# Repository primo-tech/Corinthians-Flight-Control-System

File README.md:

# Corinthians-Flight-Control-System
Raspberry Pi Zero W + STM32F103C8T6 Based Flight Control System For Fixed wing and Multi-Rotor UAVs

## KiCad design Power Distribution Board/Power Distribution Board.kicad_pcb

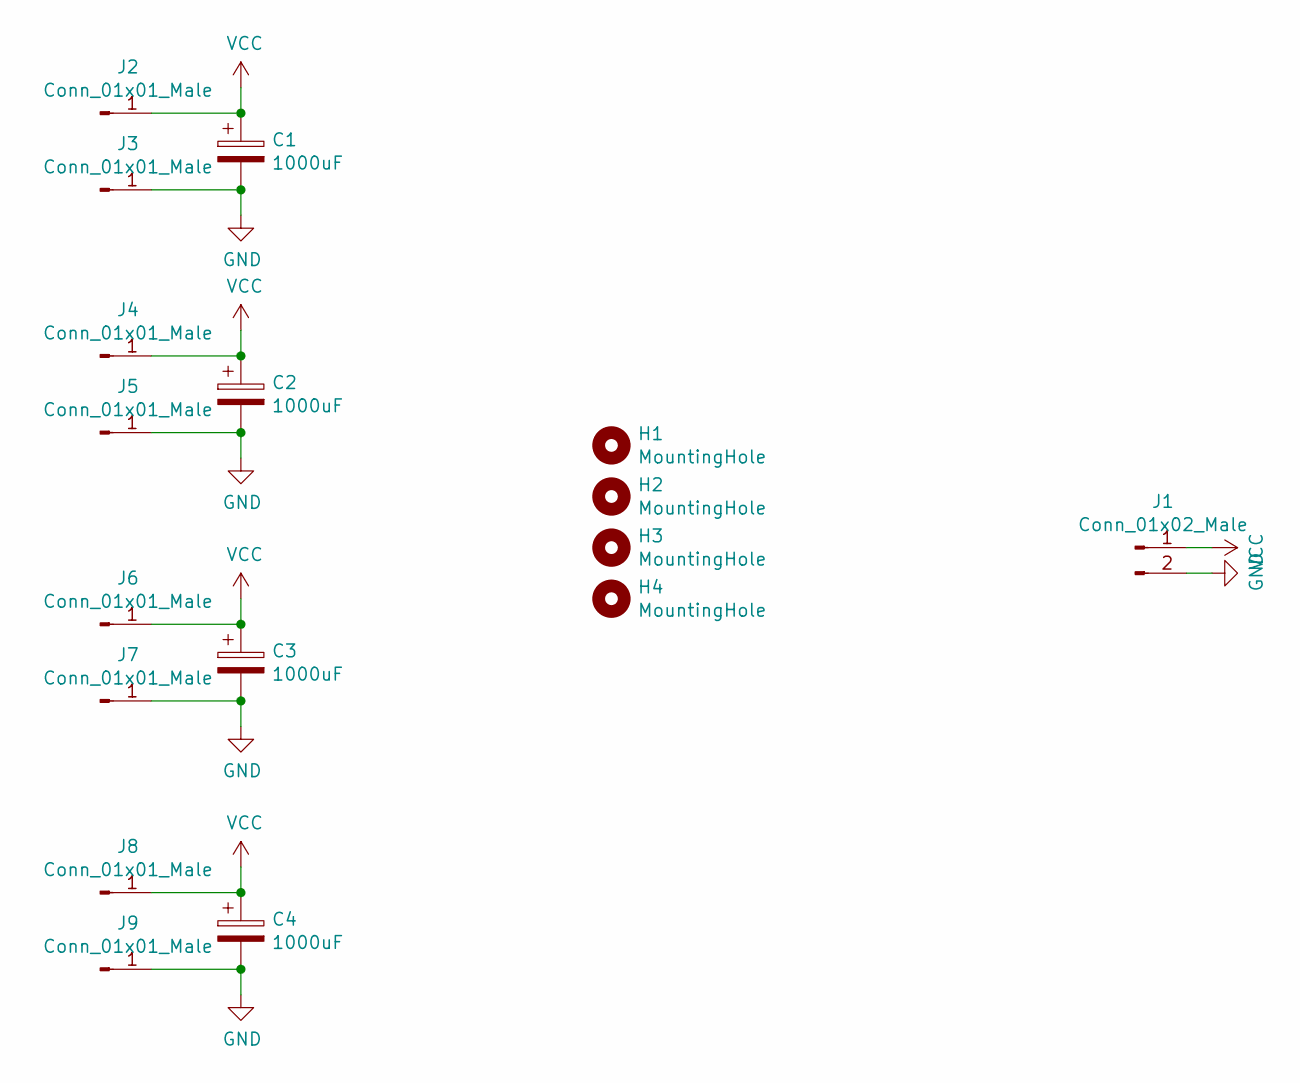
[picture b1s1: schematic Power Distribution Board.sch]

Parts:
C1, C2, C3, C4: 1000uF; CP_Radial_D10.0mm_P7.50mm
H1, H2, H3, H4: MountingHole; MountingHole_3.2mm_M3
J1: Conn_01x02_Male; AMASS_XT60-M_1x02_P7.20mm_Vertical
J2, J3, J4, J5, J6, J7, J8, J9: Conn_01x01_Male; TestPoint_Pad_4.0x4.0mm

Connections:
GND: C1.2, C2.2, C3.2, C4.2, J1.2, J3.1, J5.1, J7.1, J9.1
VCC: C1.1, C2.1, C3.1, C4.1, J1.1, J2.1, J4.1, J6.1, J8.1

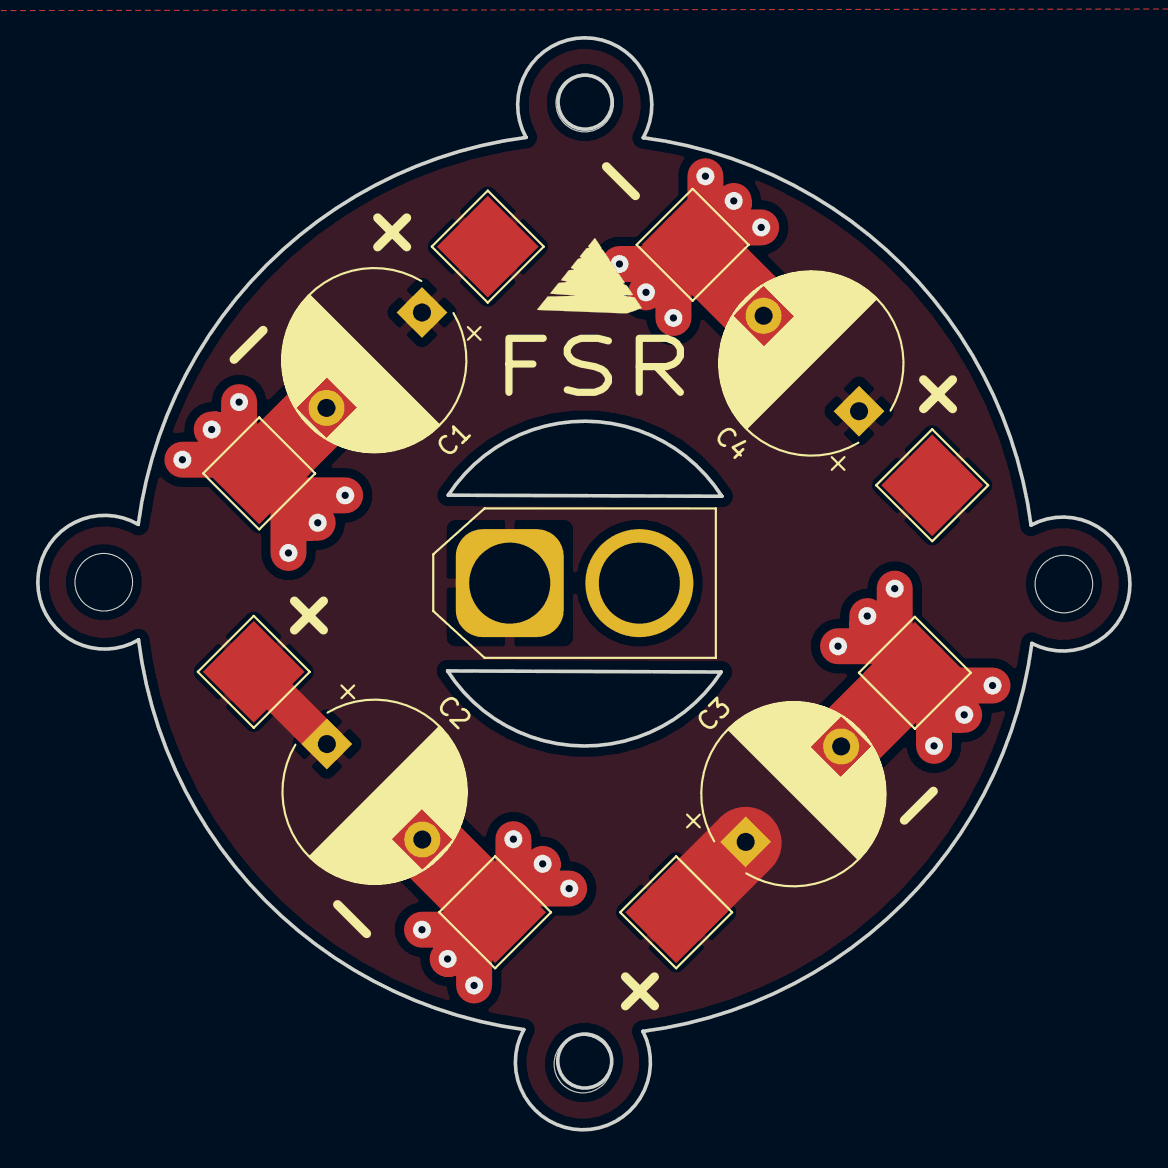
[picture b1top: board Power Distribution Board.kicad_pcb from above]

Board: 2 copper layers, 60.7 x 60.7 mm, 17 parts (0 on the bottom side), 2 nets.

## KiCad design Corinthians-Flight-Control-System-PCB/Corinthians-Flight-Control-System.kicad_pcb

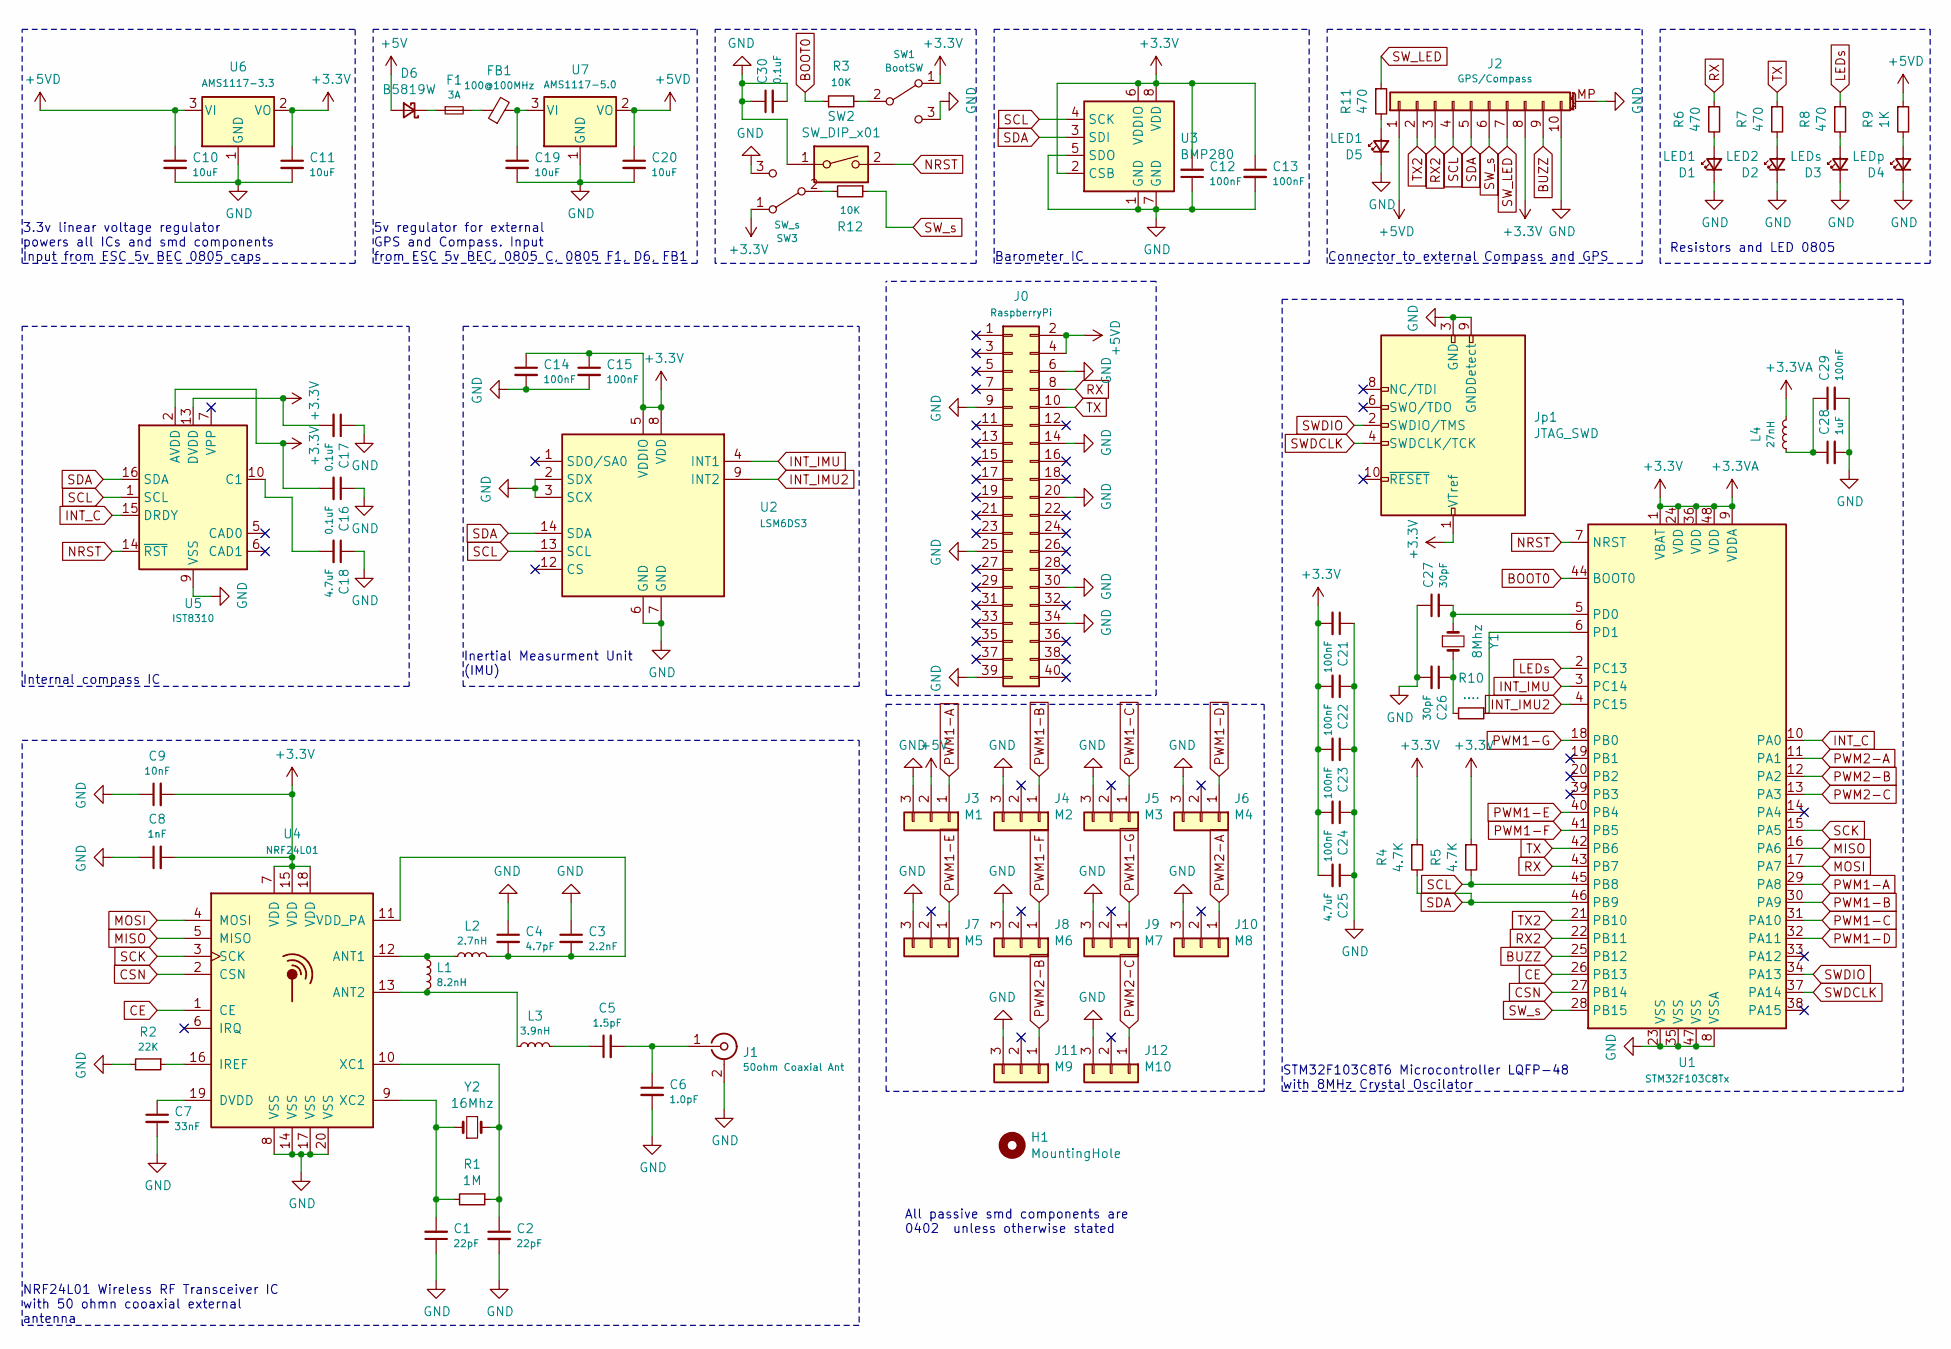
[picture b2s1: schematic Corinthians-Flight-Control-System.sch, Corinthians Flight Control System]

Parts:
C1, C2: 22pF; C_0402_1005Metric
C3: 2.2nF; C_0402_1005Metric
C4: 4.7pF; C_0402_1005Metric
C5: 1.5pF; C_0402_1005Metric
C6: 1.0pF; C_0402_1005Metric
C7: 33nF; C_0402_1005Metric
C8: 1nF; C_0402_1005Metric
C9: 10nF; C_0402_1005Metric
C10, C11, C19, C20: 10uF; C_0805_2012Metric
C12, C13, C14, C15, C21, C22, C23, C24, C29: 100nF; C_0402_1005Metric
C16, C17, C30: 0.1uF; C_0402_1005Metric
C18, C25: 4.7uF; C_0402_1005Metric
C26, C27: 30pF; C_0402_1005Metric
C28: 1uF; C_0402_1005Metric
D1: LED1; LED_0805_2012Metric
D2: LED2; LED_0805_2012Metric
D3: LEDs; LED_0805_2012Metric
D4: LEDp; LED_0805_2012Metric
D5: LED1; LED_0402_1005Metric
D6: B5819W; D_0805_2012Metric
F1: 3A; Fuse_0805_2012Metric
FB1: 100@100MHz; L_0805_2012Metric
H1: MountingHole; MountingHole_3.2mm_M3
J0: RaspberryPi; PinSocket_2x20_P2.54mm_Vertical
J1: 50ohm Coaxial Ant; SMA_Molex_73251-2200_Horizontal
J2: GPS/Compass; JST_GH_BM10B-GHS-TBT_1x10-1MP_P1.25mm_Vertical
J3: M1; PinHeader_1x03_P2.54mm_Vertical
J4: M2; PinHeader_1x03_P2.54mm_Vertical
J5: M3; PinHeader_1x03_P2.54mm_Vertical
J6: M4; PinHeader_1x03_P2.54mm_Vertical
J7: M5; PinHeader_1x03_P2.54mm_Vertical
J8: M6; PinHeader_1x03_P2.54mm_Vertical
J9: M7; PinHeader_1x03_P2.54mm_Vertical
J10: M8; PinHeader_1x03_P2.54mm_Vertical
J11: M9; PinHeader_1x03_P2.54mm_Vertical
J12: M10; PinHeader_1x03_P2.54mm_Vertical
Jp1: JTAG_SWD; PinHeader_2x05_P2.54mm_Vertical
L1: 8.2nH; L_0402_1005Metric
L2: 2.7nH; L_0402_1005Metric
L3: 3.9nH; L_0402_1005Metric
L4: 27nH; L_0402_1005Metric
R1: 1M; R_0402_1005Metric
R2: 22K; R_0402_1005Metric
R3, R12: 10K; R_0402_1005Metric
R4, R5: 4.7K; R_0402_1005Metric
R6, R7, R8: 470; R_0805_2012Metric
R9: 1K; R_0805_2012Metric
R10: ....; R_0402_1005Metric
R11: 470; R_0402_1005Metric
SW1: BootSW; SW_DIP_SPSTx01_Slide_Copal_CVS-01xB_W5.9mm_P1mm
SW2: SW_DIP_x01; SW_SPST_CK_RS282G05A3
SW3: SW_s; SW_DIP_SPSTx01_Slide_Copal_CVS-01xB_W5.9mm_P1mm
U1: STM32F103C8Tx; LQFP-48_7x7mm_P0.5mm
U2: LSM6DS3; LGA-14_3x2.5mm_P0.5mm_LayoutBorder3x4y
U3: BMP280; Bosch_LGA-8_2x2.5mm_P0.65mm_ClockwisePinNumbering
U4: NRF24L01; QFN-20-1EP_4x4mm_P0.5mm_EP2.5x2.5mm
U5: IST8310; LGA-16_3x3mm_P0.5mm
U6: AMS1117-3.3; SOT-223-3_TabPin2
U7: AMS1117-5.0; SOT-223-3_TabPin2
Y1: 8Mhz; Crystal_SMD_0603-2Pin_6.0x3.5mm
Y2: 16Mhz; Crystal_SMD_0603-2Pin_6.0x3.5mm

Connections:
+3.3VA: C8.2, C9.2, C11.1, C12.2, C13.1, C14.1, C15.1, C16.2, C17.2, C21.2, C22.2, C23.2, C24.2, C25.2, J2.8, Jp1.1 (VTref), L4.2, R4.1, R5.1, SW1.1 (A), SW3.1 (A), U1.1 (VBAT), U1.9 (VDDA), U1.24 (VDD), U1.36 (VDD), U1.48 (VDD), U2.5 (VDDIO), U2.8 (VDD), U3.2 (CSB), U3.6 (VDDIO), U3.8 (VDD), U4.7 (VDD), U4.15 (VDD), U4.18 (VDD), U5.2 (AVDD), U5.13 (DVDD), U6.2 (VO)
+5V: D6.2 (A), J3.2
+5VD: C10.1, C20.1, J0.2, J0.4, J2.1, R9.1, U6.3 (VI), U7.2 (VO)
BOOT0: R3.1, U1.44 (BOOT0)
BUZZ: J2.9, U1.25 (PB12)
CE: U1.26 (PB13), U4.1 (CE)
CSN: U1.27 (PB14), U4.2 (CSN)
GND: C1.1, C2.2, C3.1, C4.1, C6.2, C7.2, C8.1, C9.1, C10.2, C11.2, C12.1, C13.2, C14.2, C15.2, C16.1, C17.1, C18.1, C19.2, C20.2, C21.1, C22.1, C23.1, C24.1, C25.1, C26.2, C27.1, C28.2, C29.2, C30.1, C30.2, D1.1 (K), D2.1 (K), D3.1 (K), D4.1 (K), D5.1 (K), J0.6, J0.9, J0.14, J0.20, J0.25, J0.30, J0.34, J0.39, J1.2 (Ext), J2.10, J2.MP (MountPin), J3.3, J4.3, J5.3, J6.3, J7.3, J8.3, J9.3, J10.3, J11.3, J12.3, Jp1.3 (GND), Jp1.5 (GND), Jp1.9 (GNDDetect), R2.2, SW1.3 (C), SW2.1, SW3.3 (C), U1.8 (VSSA), U1.23 (VSS), U1.35 (VSS), U1.47 (VSS), U2.2 (SDX), U2.3 (SCX), U2.6 (GND), U2.7 (GND), U3.1 (GND), U3.5 (SDO), U3.7 (GND), U4.8 (VSS), U4.14 (VSS), U4.17 (VSS), U4.20 (VSS), U5.9 (VSS), U5.11 (VSS), U6.1 (GND), U7.1 (GND)
INT_C: U1.10 (PA0), U5.15 (DRDY)
INT_IMU: U1.3 (PC14), U2.4 (INT1)
INT_IMU2: U1.4 (PC15), U2.9 (INT2)
LEDs: R8.1, U1.2 (PC13)
MISO: U1.16 (PA6), U4.5 (MISO)
MOSI: U1.17 (PA7), U4.4 (MOSI)
NRST: SW2.2, U1.7 (NRST), U5.14 (~RST)
unnamed: C1.2, R1.2, U4.9 (XC2), Y2.1
unnamed: C2.1, R1.1, U4.10 (XC1), Y2.2
unnamed: C3.2, C4.2, L2.2, U4.11 (VDD_PA)
unnamed: C5.1, L3.2
unnamed: C5.2, C6.1, J1.1 (In)
unnamed: C7.1, U4.19 (DVDD)
unnamed: C18.2, U5.10 (C1)
unnamed: C19.1, FB1.2, U7.3 (VI)
unnamed: C26.1, R10.2, Y1.2
unnamed: C27.2, U1.5 (PD0), Y1.1
unnamed: C28.1, C29.1, L4.1
unnamed: D1.2 (A), R6.2
unnamed: D2.2 (A), R7.2
unnamed: D3.2 (A), R8.2
unnamed: D4.2 (A), R9.2
unnamed: D5.2 (A), R11.2
unnamed: D6.1 (K), F1.1
unnamed: F1.2, FB1.1
unnamed: L1.1, L2.1, U4.12 (ANT1)
unnamed: L1.2, L3.1, U4.13 (ANT2)
unnamed: R2.1, U4.16 (IREF)
unnamed: R3.2, SW1.2 (B)
unnamed: R10.1, U1.6 (PD1)
unnamed: R12.2, SW3.2 (B)
PWM1-A: J3.1, U1.29 (PA8)
PWM1-B: J4.1, U1.30 (PA9)
PWM1-C: J5.1, U1.31 (PA10)
PWM1-D: J6.1, U1.32 (PA11)
PWM1-E: J7.1, U1.40 (PB4)
PWM1-F: J8.1, U1.41 (PB5)
PWM1-G: J9.1, U1.18 (PB0)
PWM2-A: J10.1, U1.11 (PA1)
PWM2-B: J11.1, U1.12 (PA2)
PWM2-C: J12.1, U1.13 (PA3)
RX: J0.8, R6.1, U1.43 (PB7)
RX2: J2.3, U1.22 (PB11)
SCK: U1.15 (PA5), U4.3 (SCK)
SCL: J2.4, R5.2, U1.45 (PB8), U2.13 (SCL), U3.4 (SCK), U5.1 (SCL)
SDA: J2.5, R4.2, U1.46 (PB9), U2.14 (SDA), U3.3 (SDI), U5.16 (SDA)
SWDCLK: Jp1.4 (SWDCLK/TCK), U1.37 (PA14)
SWDIO: Jp1.2 (SWDIO/TMS), U1.34 (PA13)
SW_LED: J2.7, R11.1
SW_s: J2.6, R12.1, U1.28 (PB15)
TX: J0.10, R7.1, U1.42 (PB6)
TX2: J2.2, U1.21 (PB10)

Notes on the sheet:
All passive smd components are 0402 unless otherwise stated
3.3v linear voltage regulator powers all ICs and smd components Input from ESC 5v BEC 0805 caps
Internal compass IC
Inertial Measurment Unit (IMU)
NRF24L01 Wireless RF Transceiver IC with 50 ohmn cooaxial external antenna
Barometer IC
Connector to external Compass and GPS
STM32F103C8T6 Microcontroller LQFP-48 with 8MHz Crystal Oscilator
5v regulator for external GPS and Compass. Input from ESC 5v BEC, 0805 C, 0805 F1, D6, FB1
Resistors and LED 0805

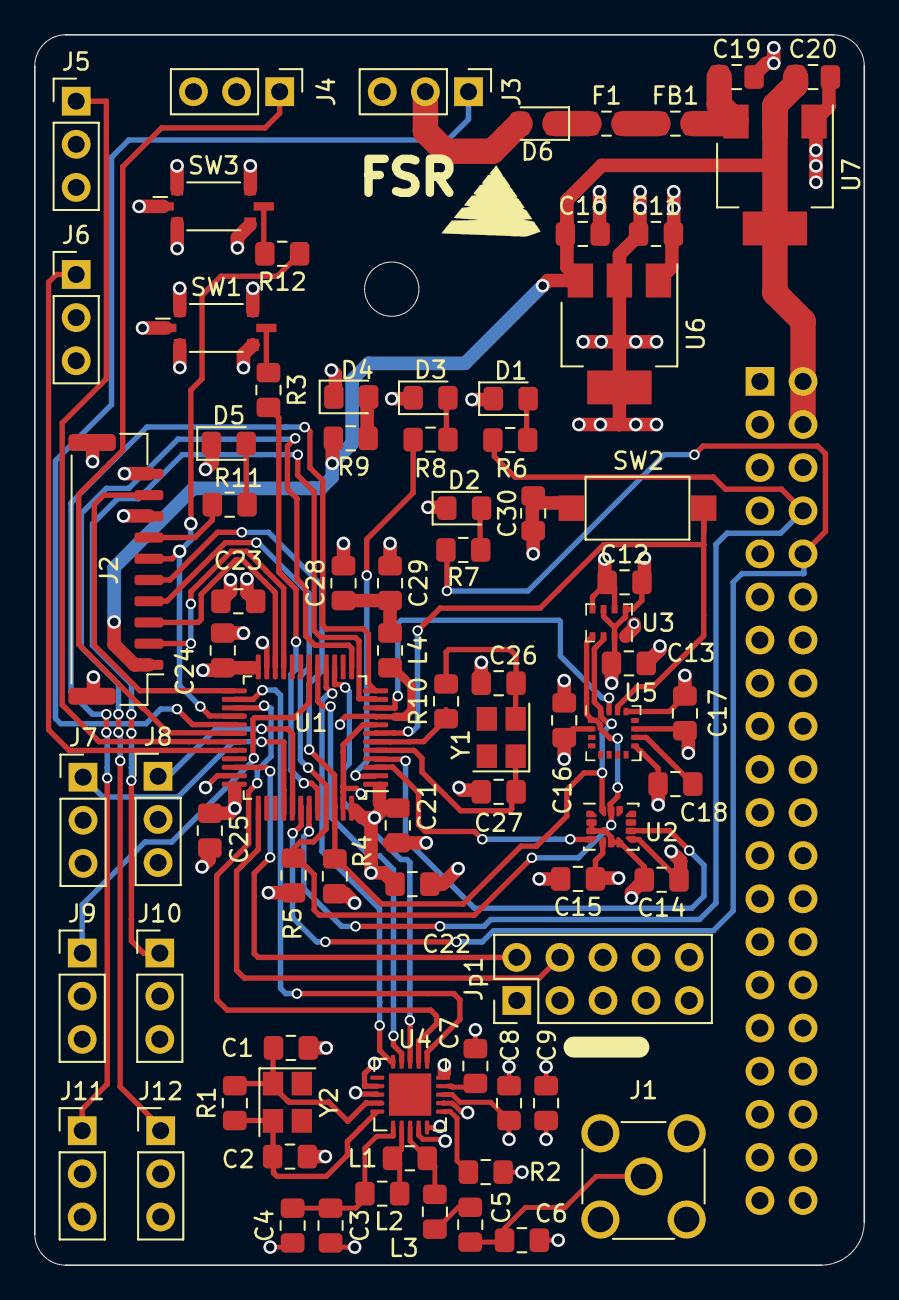
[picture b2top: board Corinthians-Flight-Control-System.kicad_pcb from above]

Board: 4 copper layers, 48.9 x 72.5 mm, 81 parts (1 on the bottom side), 60 nets.

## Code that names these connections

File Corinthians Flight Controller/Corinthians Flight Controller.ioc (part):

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Mcu.Name=STM32F103C(8-B)Tx
Mcu.Package=LQFP48
Mcu.UserName=STM32F103C8Tx
PA0-WKUP.GPIOParameters=GPIO_PuPd,GPIO_ModeDefaultEXTI
PA0-WKUP.GPIO_ModeDefaultEXTI=GPIO_MODE_IT_RISING
PA0-WKUP.GPIO_PuPd=GPIO_NOPULL
PA0-WKUP.Signal=GPXTI0
PA1.Signal=S_TIM2_CH2
PA10.Signal=S_TIM1_CH3
PA11.Signal=S_TIM1_CH4
PA13.Mode=Serial_Wire
PA13.Signal=SYS_JTMS-SWDIO
PA14.Mode=Serial_Wire
PA14.Signal=SYS_JTCK-SWCLK
PA2.Signal=S_TIM2_CH3
PA3.Signal=S_TIM2_CH4
PA5.Mode=Full_Duplex_Master
PA5.Signal=SPI1_SCK
PA6.Mode=Full_Duplex_Master
PA6.Signal=SPI1_MISO
PA7.Mode=Full_Duplex_Master
PA7.Signal=SPI1_MOSI
PA8.Signal=S_TIM1_CH1
PA9.Signal=S_TIM1_CH2
PB0.Signal=S_TIM3_CH3
PB10.Mode=Asynchronous
PB10.Signal=USART3_TX
PB11.Mode=Asynchronous
PB11.Signal=USART3_RX
PB12.GPIOParameters=GPIO_Speed,PinState,GPIO_PuPd,GPIO_Label,GPIO_ModeDefaultOutputPP
PB12.GPIO_Label=Buzzer
PB12.GPIO_ModeDefaultOutputPP=GPIO_MODE_OUTPUT_PP
PB12.GPIO_PuPd=GPIO_NOPULL
PB12.GPIO_Speed=GPIO_SPEED_FREQ_LOW
PB12.PinState=GPIO_PIN_RESET
PB12.Signal=GPIO_Output
PB13.GPIOParameters=GPIO_Speed,PinState,GPIO_PuPd,GPIO_Label,GPIO_ModeDefaultOutputPP
PB13.GPIO_Label=NRF-CE
PB13.GPIO_ModeDefaultOutputPP=GPIO_MODE_OUTPUT_PP
PB13.GPIO_PuPd=GPIO_NOPULL
PB13.GPIO_Speed=GPIO_SPEED_FREQ_LOW
PB13.PinState=GPIO_PIN_RESET
PB13.Signal=GPIO_Output
PB14.GPIOParameters=GPIO_Speed,PinState,GPIO_PuPd,GPIO_Label,GPIO_ModeDefaultOutputPP
PB14.GPIO_Label=NRF-CSN
PB14.GPIO_ModeDefaultOutputPP=GPIO_MODE_OUTPUT_PP
PB14.GPIO_PuPd=GPIO_NOPULL
PB14.GPIO_Speed=GPIO_SPEED_FREQ_LOW
PB14.PinState=GPIO_PIN_RESET
PB14.Signal=GPIO_Output
PB15.GPIOParameters=GPIO_Speed,PinState,GPIO_PuPd,GPIO_Label,GPIO_ModeDefaultOutputPP
PB15.GPIO_Label=GPS-Switch
PB15.GPIO_ModeDefaultOutputPP=GPIO_MODE_OUTPUT_PP
PB15.GPIO_PuPd=GPIO_NOPULL
PB15.GPIO_Speed=GPIO_SPEED_FREQ_LOW
PB15.PinState=GPIO_PIN_RESET
PB15.Signal=GPIO_Output
PB4.Signal=S_TIM3_CH1
PB5.Signal=S_TIM3_CH2
PB6.Mode=Asynchronous
PB6.Signal=USART1_TX
PB7.Mode=Asynchronous
PB7.Signal=USART1_RX
PB8.Mode=I2C
PB8.Signal=I2C1_SCL
PB9.Mode=I2C
PB9.Signal=I2C1_SDA
PC13-TAMPER-RTC.GPIOParameters=GPIO_Speed,PinState,GPIO_PuPd,GPIO_ModeDefaultOutputPP
PC13-TAMPER-RTC.GPIO_ModeDefaultOutputPP=GPIO_MODE_OUTPUT_PP
PC13-TAMPER-RTC.GPIO_PuPd=GPIO_NOPULL
PC13-TAMPER-RTC.GPIO_Speed=GPIO_SPEED_FREQ_LOW
PC13-TAMPER-RTC.PinState=GPIO_PIN_RESET
PC13-TAMPER-RTC.Signal=GPIO_Output
PC14-OSC32_IN.GPIOParameters=GPIO_PuPd,GPIO_ModeDefaultEXTI
PC14-OSC32_IN.GPIO_ModeDefaultEXTI=GPIO_MODE_IT_RISING
PC14-OSC32_IN.GPIO_PuPd=GPIO_NOPULL
PC14-OSC32_IN.Signal=GPXTI14
PC15-OSC32_OUT.GPIOParameters=GPIO_PuPd,GPIO_ModeDefaultEXTI
PC15-OSC32_OUT.GPIO_ModeDefaultEXTI=GPIO_MODE_IT_RISING
PC15-OSC32_OUT.GPIO_PuPd=GPIO_NOPULL
PC15-OSC32_OUT.Signal=GPXTI15
PD0-OSC_IN.Mode=HSE-External-Oscillator
PD0-OSC_IN.Signal=RCC_OSC_IN
PD1-OSC_OUT.Mode=HSE-External-Oscillator
PD1-OSC_OUT.Signal=RCC_OSC_OUT
RCC.SYSCLKFreq_VALUE=72000000
RCC.SYSCLKSource=RCC_SYSCLKSOURCE_PLLCLK
board=custom

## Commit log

2021-07-13 Initital Upload
    PCB Files and Datasheets initial commit
2021-08-01 New corrections and CAD files
2021-08-02 STM32CubeIDE Configuration Software
2021-08-02 FreeRTOS TIM4 Clock + STM32 Datasheet
2021-08-03 reference manual stm32f103
2021-08-12 Timer DMA Removed: Unnecessary
2021-08-19 schematic and pcb routing update
2021-08-22 Routing finished ?
2021-08-22 updated 3d modeld
2021-08-22 DRC Check
2021-08-22 new post routing images
2021-09-20 Logo Footprints Added
2021-10-18 0402 components changed to 0805
2021-10-20 New BOM and Images
2021-10-20 deselected components
2021-10-21 Post DRC Check
2021-10-23 Images Folder Added
2021-10-30 clean
2021-12-31 updates and new power distribution pcb
